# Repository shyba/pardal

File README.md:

# Pardal PCB

Command-line PCB place & route tool with a Python API and a Mojo backend route path.

## What this project covers

- Python-native board construction and routing workflows
- CLI flows for `build`, `place`, `route`, `drc`, and `repl`
- FreeRouting interop (`freeroute`)
- Mojo backend routing (`backend-route`) using KiCad 9 in Docker for extract/apply

## Requirements

- Python 3.10+
- Docker (required for `backend-route` and `freeroute`)
- KiCad on host is optional for backend-route/freeroute (Docker supplies KiCad 9 there)
- System `pcbnew` is required for `pardal-finalize`

## KiCad compatibility

- Full supported path: KiCad 9 (native or Docker-based tooling)
- Current default backend route path uses Docker image `kicad/kicad:9.0.6-full`
- Older host KiCad versions may still work for limited flows, but are not the full baseline

## Install

```bash
python3 -m venv venv
./venv/bin/pip install -U pip
./venv/bin/pip install -e .
```

Optional global shortcut:

```bash
pip install -e .
pardal --help
```

## CLI quickstart

```bash
# Show commands
./venv/bin/python -m pardal.cli --help

# Build from netlist (+ optional route)
pardal build project.net -p placement.txt -o board.kicad_pcb
pardal build project.net -p placement.txt -o board.kicad_pcb --route

# Route an existing PCB
pardal route board.kicad_pcb -o board_routed.kicad_pcb

# Run DRC
pardal drc board_routed.kicad_pcb --format text

# REPL
pardal repl
```

## Route DSL workflow

The route DSL commands stage artifacts only. They are not release-ready, JLC-ready, or orderable claims.

```bash
# Seed the checked-in example directory
pardal route-dsl example init --example-dir examples/routing_dsl

# Assemble the example artifacts and print the manifest path
pardal route-dsl example run --example-dir examples/routing_dsl

# Pure artifact stages
pardal route-dsl board-ir examples/routing_dsl/board_source.json -o examples/routing_dsl/board.ir.json
pardal route-dsl plan examples/routing_dsl/routes.pdl.yaml examples/routing_dsl/board.ir.json examples/routing_dsl/backend_manifest.json --route-plan-output examples/routing_dsl/route-plan.ir.json --artifact-output examples/routing_dsl/capability-report.json
pardal route-dsl candidates examples/routing_dsl/board.ir.json examples/routing_dsl/route-plan.ir.json examples/routing_dsl/backend_manifest.json -o examples/routing_dsl/route-candidates.json --routes examples/routing_dsl/routes.json

# Apply-to-copy: validate first, then copy input board bytes to the output board path and still write an apply report
pardal route-dsl apply examples/routing_dsl/board.ir.json examples/routing_dsl/route-plan.ir.json examples/routing_dsl/route-candidates.json -o examples/routing_dsl/apply-report.json --selected-candidate-id cand_rg_fpc_escape_a_0001 --input-board input.kicad_pcb --output-board output.kicad_pcb

# fpga-large staged finish-readiness lane
pardal route-dsl fpga-large prepare --work-dir /tmp/pardal-fpga-large
pardal route-dsl fpga-large resume --work-dir /tmp/pardal-fpga-large
pardal route-dsl fpga-large report --work-dir /tmp/pardal-fpga-large
```

## Mojo backend route quickstart

Routes an existing `.kicad_pcb` by extracting with KiCad 9 in Docker, routing on host backend, then applying back with KiCad 9 in Docker.

```bash
pardal backend-route input.kicad_pcb \
  -o output.kicad_pcb \
  --docker-image kicad/kicad:9.0.6-full \
  --cfg tests/fixtures/parity_fixtures/mojo_cfgs/strict_spacing.json \
  --extract-timeout-s 120 \
  --route-timeout-s 120 \
  --apply-timeout-s 120
```

Useful debug artifacts:

- `--problem-json /path/problem.json`
- `--routes-json /path/routes.json`

Deprecated alias:

- `pardal rust-route` (same behavior as `backend-route`, kept for compatibility)

## Python API quickstart

```python
from pathlib import Path
from pardal.board_builder import fpga_board
from pardal.routing_strategies import route_board
from pardal.kicad_writer import KicadWriter

board = (fpga_board(layers=4, width=40, height=40)
    .component("U1", "TQFP-32", (20, 20), value="FPGA")
    .component("C1", "0603", (12, 20), value="100nF")
    .net("VCC", "Power", [("U1", "8"), ("C1", "1")])
    .net("GND", "Power", [("U1", "16"), ("C1", "2")])
    .build())

result = route_board(board, "fpga")
print(f"Routed {result.nets_routed}/{result.nets_total} nets")

KicadWriter().write(board, Path("board.kicad_pcb"))
```

## Atopile handoff (minimal)

```bash
# Use the placed board produced by ato build
pardal route build/builds/default/default/default.kicad_pcb -o board_routed.kicad_pcb

# Optional: backend route instead of Python router
pardal backend-route build/builds/default/default/default.kicad_pcb -o board_routed.kicad_pcb

# Finalization uses system Python + pcbnew
/usr/bin/python3 -m pardal.finalize board_routed.kicad_pcb board_final.kicad_pcb
```

## Finalization

`pardal-finalize` (or `python -m pardal.finalize`) is the production-oriented step that replaces simplified footprints and rebuilds zones using system `pcbnew`.

## Testing

Fast checks:

```bash
./venv/bin/python -m pytest -q tests/test_cli.py tests/test_repl.py tests/test_api_io.py tests/test_route_command.py
./venv/bin/python -m pytest -q tests/integration/test_routing_scenarios.py tests/integration/test_variable_widths.py
```

## Troubleshooting

- `Error: docker permission denied`: ensure your user can access Docker daemon.
- `backend-route timed out`: increase `--extract-timeout-s`, `--route-timeout-s`, and `--apply-timeout-s`.
- Missing backend binary/config behavior: run without `--cfg` first, then add config incrementally.

## License

GNU Affero General Public License v3.0 (AGPL-3.0). See `LICENSE`.

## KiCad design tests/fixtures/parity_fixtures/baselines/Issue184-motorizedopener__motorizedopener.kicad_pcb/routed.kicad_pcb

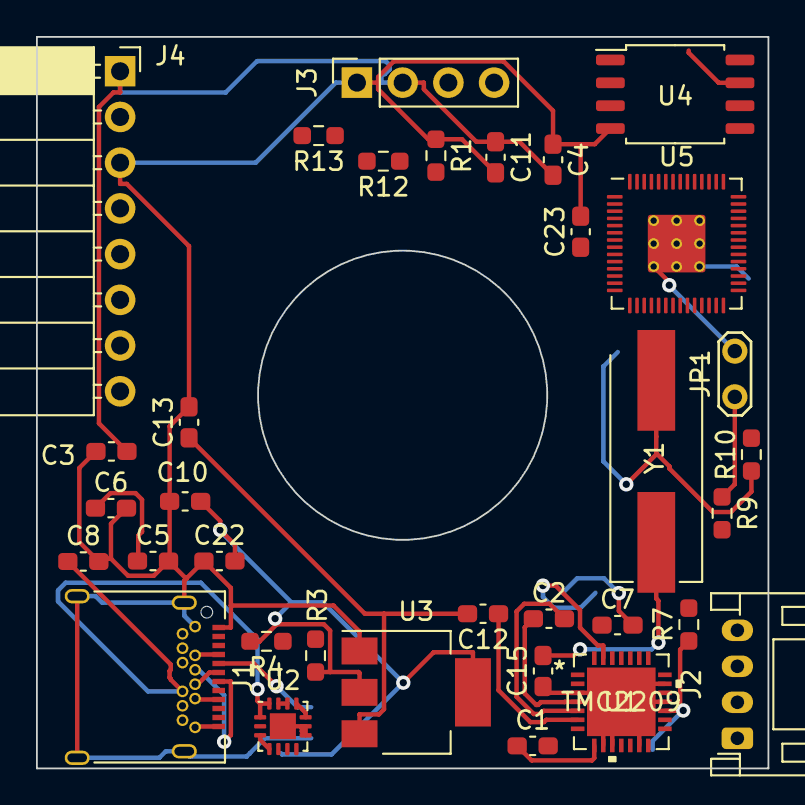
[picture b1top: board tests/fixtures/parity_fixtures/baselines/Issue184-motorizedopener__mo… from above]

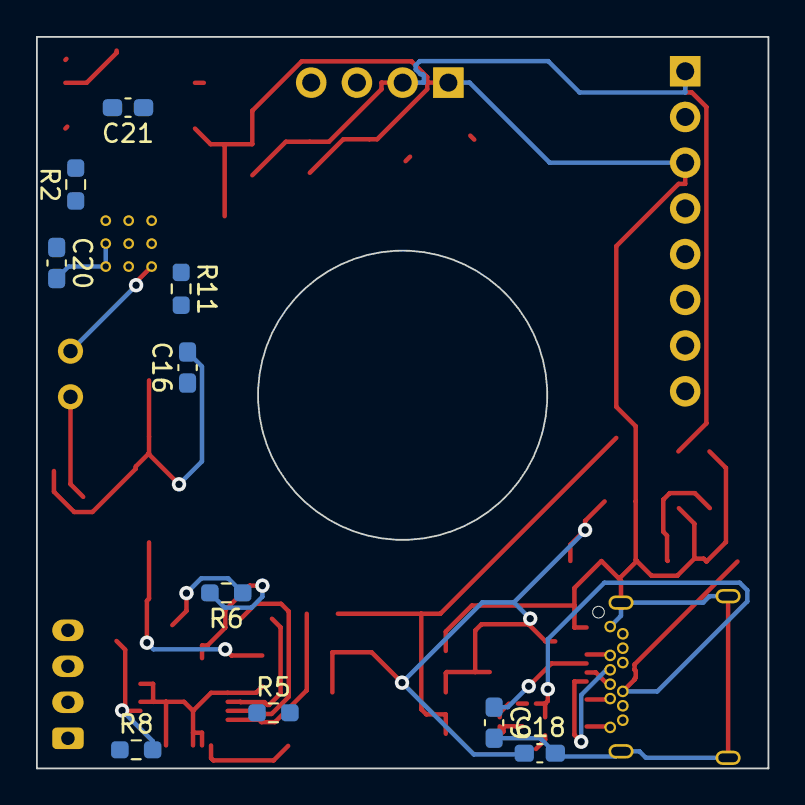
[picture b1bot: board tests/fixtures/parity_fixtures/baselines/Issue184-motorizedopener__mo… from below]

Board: 2 copper layers, 40.6 x 40.6 mm, 44 parts (10 on the bottom side), 49 nets.

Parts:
C1: 2.2uF; C_0603_1608Metric_Pad1.08x0.95mm_HandSolder
C2, C12: 22nF; C_0603_1608Metric_Pad1.08x0.95mm_HandSolder
C3, C21, C22: 1uF; C_0603_1608Metric_Pad1.08x0.95mm_HandSolder
C4, C6: 0.1uF; C_0603_1608Metric_Pad1.08x0.95mm_HandSolder
C5, C7, C11: 10uF; C_0603_1608Metric_Pad1.08x0.95mm_HandSolder
C8, C9: 470pF; C_0603_1608Metric_Pad1.08x0.95mm_HandSolder
C10, C18: 100nF; C_0603_1608Metric_Pad1.08x0.95mm_HandSolder
C13: 300nF; C_0603_1608Metric_Pad1.08x0.95mm_HandSolder
C15, C16: 27pF; C_0603_1608Metric_Pad1.08x0.95mm_HandSolder
C20: 200nF; C_0603_1608Metric_Pad1.08x0.95mm_HandSolder
C23: 700nF; C_0603_1608Metric_Pad1.08x0.95mm_HandSolder
J1: USB_C_Receptacle; USB_C_Receptacle_Amphenol_12401548E4-2A
J2: Stepper OUT; JST_PH_S4B-PH-K_1x04_P2.00mm_Horizontal
J3: I2C OLED; PinSocket_1x04_P2.54mm_Vertical
J4: SPI RFID; PinSocket_1x08_P2.54mm_Horizontal
JP1: Jumper_2_Open; TestPoint_2Pads_Pitch2.54mm_Drill0.8mm
R1, R7: 10k; R_0603_1608Metric_Pad0.98x0.95mm_HandSolder
R2, R3, R4: 4.7k; R_0603_1608Metric_Pad0.98x0.95mm_HandSolder
R5, R6: 220m; R_0603_1608Metric_Pad0.98x0.95mm_HandSolder
R8: 4.4k; R_0603_1608Metric_Pad0.98x0.95mm_HandSolder
R9, R10, R11: 1k; R_0603_1608Metric_Pad0.98x0.95mm_HandSolder
R12, R13: 27.4; R_0603_1608Metric_Pad0.98x0.95mm_HandSolder
U1: TMC2209
U2: FUSB302B01MPX; WQFN-14-1EP_2.5x2.5mm_P0.5mm_EP1.45x1.45mm
U3: NCP1117-3.3_SOT223; SOT-223-3_TabPin2
U4: W25Q128JVS; SOIC-8_5.23x5.23mm_P1.27mm
U5: RP2040; RP2040-QFN-56
Y1: 12.000MHZ; Crystal_SMD_HC49-US

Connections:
+1V1: C20.1, C21.2, U5.23 (DVDD), U5.45 (VREG_VOUT), U5.50 (DVDD)
+3V3: C3.2, C4.2, C10.1, C11.1, C18.1, C22.2, C23.1, J3.2, J4.1, R2.2, R3.2, R4.2, R7.2, U1.15 (VCC_IO), U2.3 (VDD), U2.4 (VDD), U3.2 (VO), U4.8 (VCC), U5.1 (IOVDD), U5.10 (IOVDD), U5.22 (IOVDD), U5.33 (IOVDD), U5.42 (IOVDD), U5.43 (ADC_AVDD), U5.44 (VREG_IN), U5.48 (USB_VDD), U5.49 (IOVDD)
GND: C1.2, C3.1, C4.1, C5.2, C6.2, C7.2, C8.2, C9.2, C10.2, C11.2, C13.2, C15.1, C16.1, C18.2, C20.2, C21.1, C22.1, C23.2, J1.A1 (GND), J1.A12 (GND), J1.B1 (GND), J1.B12 (GND), J1.S1 (SHIELD), J3.1, J4.3, JP1.1 (A), R1.1, R5.1, R6.1, R8.1, U1.3 (GND), U1.9 (MS1_AD0), U1.10 (MS2_AD1), U1.13 (CLK), U1.18 (GND), U1.20 (STDBY), U1.29 (GND), U2.8 (GND), U2.9 (GND), U2.15 (GND), U3.1 (GND), U4.4 (GND), U5.19 (TESTEN), U5.57 (GND)
unnamed: C1.1, U1.8 (5VOUT)
unnamed: C2.1, U1.4 (CPO)
unnamed: C2.2, U1.5 (CPI)
unnamed: C5.1, C6.1, U2.12 (VCONN), U2.13 (VCONN)
unnamed: C12.1, U1.6 (VCP)
unnamed: C15.2, U5.20 (XIN), Y1.1
unnamed: C16.2, R10.1, Y1.2
unnamed: J2.1, U1.26 (OB1)
unnamed: J2.2, U1.24 (OA1)
unnamed: J2.3, U1.21 (OA2)
unnamed: J2.4, U1.1 (OB2)
unnamed: J3.3, U5.30 (GPIO19)
unnamed: J3.4, U5.29 (GPIO18)
unnamed: J4.2, U5.9 (GPIO7)
unnamed: J4.4, U5.14 (GPIO11)
unnamed: J4.5, U5.15 (GPIO12)
unnamed: J4.6, U5.13 (GPIO10)
unnamed: J4.7, U5.16 (GPIO13)
unnamed: JP1.2 (B), R9.1
unnamed: R5.2, U1.23 (BRA)
unnamed: R6.2, U1.27 (BRB)
unnamed: R7.1, R8.2, U1.17 (VREF)
unnamed: R9.2, U4.1 (~CS), U5.56 (QSPI_SS)
unnamed: R10.2, U5.21 (XOUT)
unnamed: R11.1, U5.11 (GPIO8)
unnamed: R12.1, U5.47 (USB_DP)
unnamed: R13.1, U5.46 (USB_DM)
unnamed: U4.2 (DO(IO1)), U5.55 (QSPI_SD1)
unnamed: U4.3 (IO2), U5.54 (QSPI_SD2)
unnamed: U4.5 (DI(IO0)), U5.53 (QSPI_SD0)
unnamed: U4.6 (CLK), U5.52 (QSPI_SCLK)
unnamed: U4.7 (IO3), U5.51 (QSPI_SD3)
PWR-INT_N: R4.1, U2.5 (INT_N), U5.31 (GPIO20)
PWR-SCL: R3.1, U2.6 (SCL), U5.28 (GPIO17)
PWR-SDA: R2.1, U2.7 (SDA), U5.27 (GPIO16)
USB-D+: J1.A6 (D+), J1.B6 (D+), R12.2
USB-D-: J1.A7 (D-), J1.B7 (D-), R13.2
VBUS: C7.1, C12.2, C13.1, J1.A4 (VBUS), J1.A9 (VBUS), J1.B4 (VBUS), J1.B9 (VBUS), U1.22 (VS), U1.28 (VS), U2.2 (VBUS), U3.3 (VI)
cc1: C9.1, J1.A5 (CC1), U2.10 (CC1), U2.11 (CC1)
cc2: C8.1, J1.B5 (CC2), U2.1 (CC2), U2.14 (CC2)
tmc_DIAG: U1.11 (DIAG), U5.39 (GPIO27_ADC1)
tmc_DIR: U1.19 (DIR), U5.17 (GPIO14)
tmc_ENN: R1.2, U1.2 (ENN), U5.8 (GPIO6)
tmc_INDEX: U1.12 (INDEX), U5.38 (GPIO26_ADC0)
tmc_STEP: U1.16 (STEP), U5.18 (GPIO15)
tmc_UART: R11.2, U1.14 (PDN_UART), U5.12 (GPIO9)

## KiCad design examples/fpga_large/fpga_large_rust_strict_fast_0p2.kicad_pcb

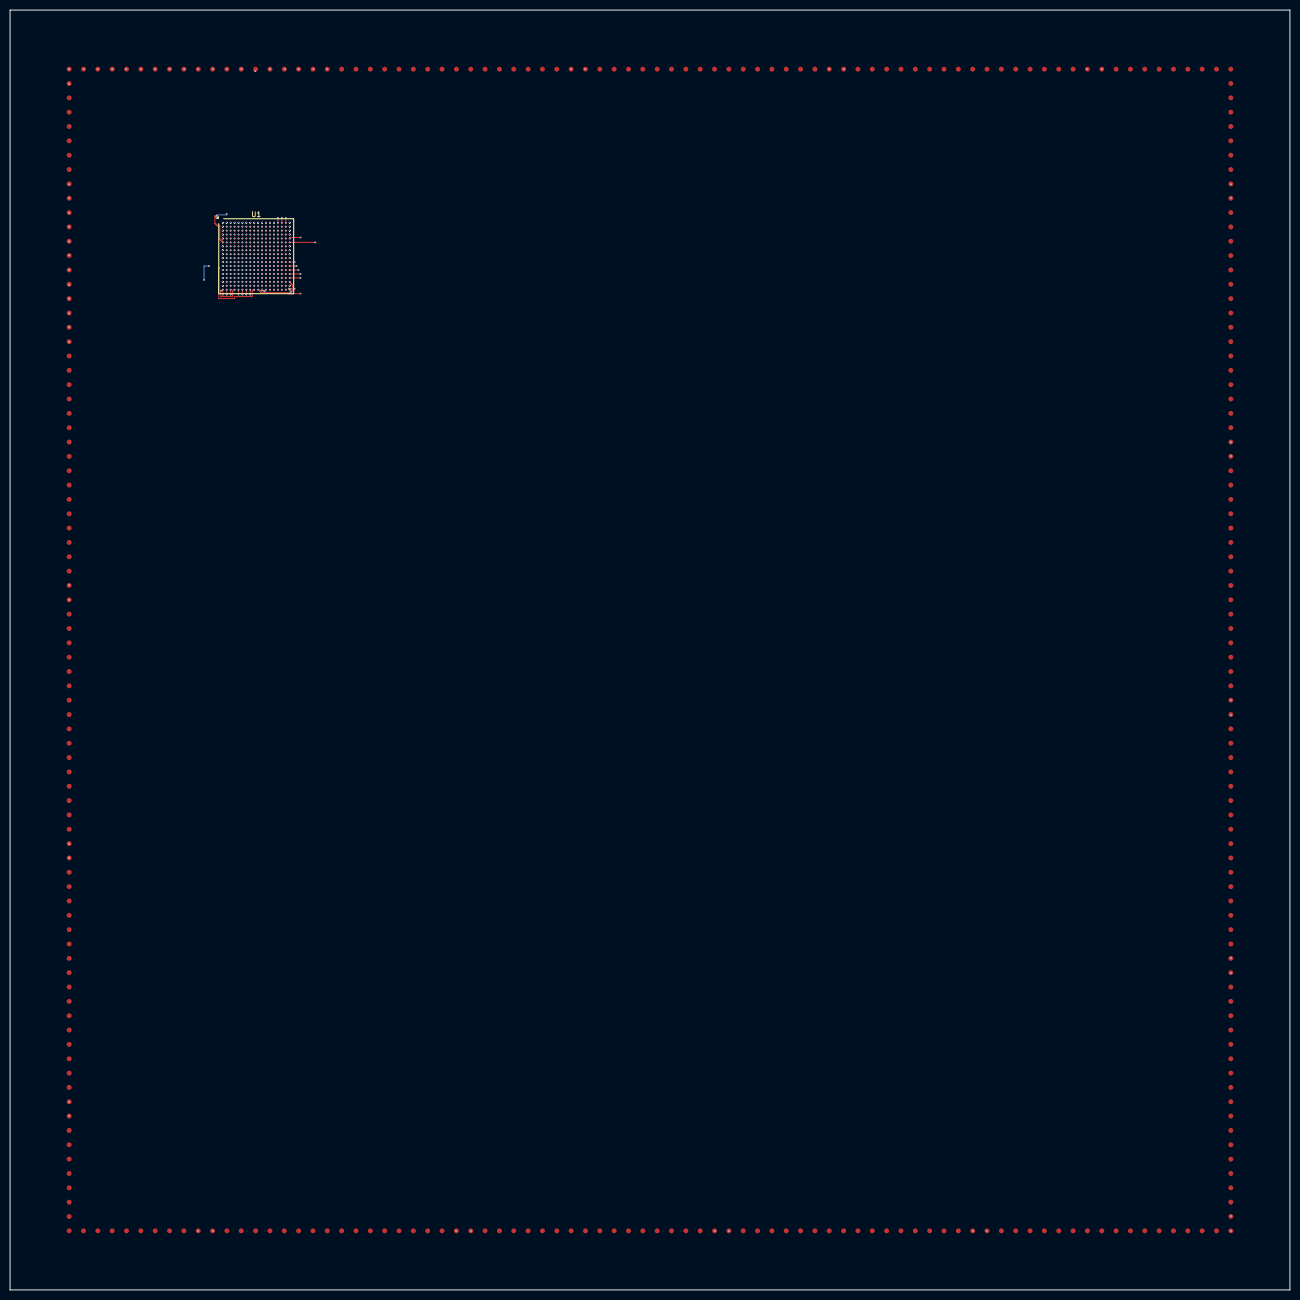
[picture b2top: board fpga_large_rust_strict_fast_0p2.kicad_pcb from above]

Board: 4 copper layers, 260.0 x 260.0 mm, 325 parts (0 on the bottom side), 324 nets.

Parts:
TP1: A1; TestPoint_Pad_D1.0mm
TP2: A2; TestPoint_Pad_D1.0mm
TP3: A3; TestPoint_Pad_D1.0mm
TP4: A4; TestPoint_Pad_D1.0mm
TP5: A5; TestPoint_Pad_D1.0mm
TP6: A6; TestPoint_Pad_D1.0mm
TP7: A7; TestPoint_Pad_D1.0mm
TP8: A8; TestPoint_Pad_D1.0mm
TP9: A9; TestPoint_Pad_D1.0mm
TP10: A10; TestPoint_Pad_D1.0mm
TP11: A11; TestPoint_Pad_D1.0mm
TP12: A12; TestPoint_Pad_D1.0mm
TP13: A13; TestPoint_Pad_D1.0mm
TP14: A14; TestPoint_Pad_D1.0mm
TP15: A15; TestPoint_Pad_D1.0mm
TP16: A16; TestPoint_Pad_D1.0mm
TP17: A17; TestPoint_Pad_D1.0mm
TP18: A18; TestPoint_Pad_D1.0mm
TP19: B1; TestPoint_Pad_D1.0mm
TP20: B2; TestPoint_Pad_D1.0mm
TP21: B3; TestPoint_Pad_D1.0mm
TP22: B4; TestPoint_Pad_D1.0mm
TP23: B5; TestPoint_Pad_D1.0mm
TP24: B6; TestPoint_Pad_D1.0mm
TP25: B7; TestPoint_Pad_D1.0mm
TP26: B8; TestPoint_Pad_D1.0mm
TP27: B9; TestPoint_Pad_D1.0mm
TP28: B10; TestPoint_Pad_D1.0mm
TP29: B11; TestPoint_Pad_D1.0mm
TP30: B12; TestPoint_Pad_D1.0mm
TP31: B13; TestPoint_Pad_D1.0mm
TP32: B14; TestPoint_Pad_D1.0mm
TP33: B15; TestPoint_Pad_D1.0mm
TP34: B16; TestPoint_Pad_D1.0mm
TP35: B17; TestPoint_Pad_D1.0mm
TP36: B18; TestPoint_Pad_D1.0mm
TP37: C1; TestPoint_Pad_D1.0mm
TP38: C2; TestPoint_Pad_D1.0mm
TP39: C3; TestPoint_Pad_D1.0mm
TP40: C4; TestPoint_Pad_D1.0mm
TP41: C5; TestPoint_Pad_D1.0mm
TP42: C6; TestPoint_Pad_D1.0mm
TP43: C7; TestPoint_Pad_D1.0mm
TP44: C8; TestPoint_Pad_D1.0mm
TP45: C9; TestPoint_Pad_D1.0mm
TP46: C10; TestPoint_Pad_D1.0mm
TP47: C11; TestPoint_Pad_D1.0mm
TP48: C12; TestPoint_Pad_D1.0mm
TP49: C13; TestPoint_Pad_D1.0mm
TP50: C14; TestPoint_Pad_D1.0mm
TP51: C15; TestPoint_Pad_D1.0mm
TP52: C16; TestPoint_Pad_D1.0mm
TP53: C17; TestPoint_Pad_D1.0mm
TP54: C18; TestPoint_Pad_D1.0mm
TP55: D1; TestPoint_Pad_D1.0mm
TP56: D2; TestPoint_Pad_D1.0mm
TP57: D3; TestPoint_Pad_D1.0mm
TP58: D4; TestPoint_Pad_D1.0mm
TP59: D5; TestPoint_Pad_D1.0mm
TP60: D6; TestPoint_Pad_D1.0mm
TP61: D7; TestPoint_Pad_D1.0mm
TP62: D8; TestPoint_Pad_D1.0mm
TP63: D9; TestPoint_Pad_D1.0mm
TP64: D10; TestPoint_Pad_D1.0mm
TP65: D11; TestPoint_Pad_D1.0mm
TP66: D12; TestPoint_Pad_D1.0mm
TP67: D13; TestPoint_Pad_D1.0mm
TP68: D14; TestPoint_Pad_D1.0mm
TP69: D15; TestPoint_Pad_D1.0mm
TP70: D16; TestPoint_Pad_D1.0mm
TP71: D17; TestPoint_Pad_D1.0mm
TP72: D18; TestPoint_Pad_D1.0mm
TP73: E1; TestPoint_Pad_D1.0mm
TP74: E2; TestPoint_Pad_D1.0mm
TP75: E3; TestPoint_Pad_D1.0mm
TP76: E4; TestPoint_Pad_D1.0mm
TP77: E5; TestPoint_Pad_D1.0mm
TP78: E6; TestPoint_Pad_D1.0mm
TP79: E7; TestPoint_Pad_D1.0mm
TP80: E8; TestPoint_Pad_D1.0mm
TP81: E9; TestPoint_Pad_D1.0mm
TP82: E10; TestPoint_Pad_D1.0mm
TP83: E11; TestPoint_Pad_D1.0mm
TP84: E12; TestPoint_Pad_D1.0mm
TP85: E13; TestPoint_Pad_D1.0mm
TP86: E14; TestPoint_Pad_D1.0mm
TP87: E15; TestPoint_Pad_D1.0mm
TP88: E16; TestPoint_Pad_D1.0mm
TP89: E17; TestPoint_Pad_D1.0mm
TP90: E18; TestPoint_Pad_D1.0mm
TP91: F1; TestPoint_Pad_D1.0mm
TP92: F2; TestPoint_Pad_D1.0mm
TP93: F3; TestPoint_Pad_D1.0mm
TP94: F4; TestPoint_Pad_D1.0mm
TP95: F5; TestPoint_Pad_D1.0mm
TP96: F6; TestPoint_Pad_D1.0mm
TP97: F7; TestPoint_Pad_D1.0mm
TP98: F8; TestPoint_Pad_D1.0mm
TP99: F9; TestPoint_Pad_D1.0mm
TP100: F10; TestPoint_Pad_D1.0mm
TP101: F11; TestPoint_Pad_D1.0mm
TP102: F12; TestPoint_Pad_D1.0mm
TP103: F13; TestPoint_Pad_D1.0mm
TP104: F14; TestPoint_Pad_D1.0mm
TP105: F15; TestPoint_Pad_D1.0mm
TP106: F16; TestPoint_Pad_D1.0mm
TP107: F17; TestPoint_Pad_D1.0mm
TP108: F18; TestPoint_Pad_D1.0mm
TP109: G1; TestPoint_Pad_D1.0mm
TP110: G2; TestPoint_Pad_D1.0mm
TP111: G3; TestPoint_Pad_D1.0mm
TP112: G4; TestPoint_Pad_D1.0mm
TP113: G5; TestPoint_Pad_D1.0mm
TP114: G6; TestPoint_Pad_D1.0mm
TP115: G7; TestPoint_Pad_D1.0mm
TP116: G8; TestPoint_Pad_D1.0mm
TP117: G9; TestPoint_Pad_D1.0mm
TP118: G10; TestPoint_Pad_D1.0mm
TP119: G11; TestPoint_Pad_D1.0mm
TP120: G12; TestPoint_Pad_D1.0mm
TP121: G13; TestPoint_Pad_D1.0mm
TP122: G14; TestPoint_Pad_D1.0mm
TP123: G15; TestPoint_Pad_D1.0mm
TP124: G16; TestPoint_Pad_D1.0mm
TP125: G17; TestPoint_Pad_D1.0mm
TP126: G18; TestPoint_Pad_D1.0mm
TP127: H1; TestPoint_Pad_D1.0mm
TP128: H2; TestPoint_Pad_D1.0mm
TP129: H3; TestPoint_Pad_D1.0mm
TP130: H4; TestPoint_Pad_D1.0mm
TP131: H5; TestPoint_Pad_D1.0mm
TP132: H6; TestPoint_Pad_D1.0mm
TP133: H7; TestPoint_Pad_D1.0mm
TP134: H8; TestPoint_Pad_D1.0mm
TP135: H9; TestPoint_Pad_D1.0mm
TP136: H10; TestPoint_Pad_D1.0mm
TP137: H11; TestPoint_Pad_D1.0mm
TP138: H12; TestPoint_Pad_D1.0mm
TP139: H13; TestPoint_Pad_D1.0mm
TP140: H14; TestPoint_Pad_D1.0mm
TP141: H15; TestPoint_Pad_D1.0mm
TP142: H16; TestPoint_Pad_D1.0mm
TP143: H17; TestPoint_Pad_D1.0mm
TP144: H18; TestPoint_Pad_D1.0mm
TP145: J1; TestPoint_Pad_D1.0mm
TP146: J2; TestPoint_Pad_D1.0mm
TP147: J3; TestPoint_Pad_D1.0mm
TP148: J4; TestPoint_Pad_D1.0mm
TP149: J5; TestPoint_Pad_D1.0mm
TP150: J6; TestPoint_Pad_D1.0mm
TP151: J7; TestPoint_Pad_D1.0mm
TP152: J8; TestPoint_Pad_D1.0mm
TP153: J9; TestPoint_Pad_D1.0mm
TP154: J10; TestPoint_Pad_D1.0mm
TP155: J11; TestPoint_Pad_D1.0mm
TP156: J12; TestPoint_Pad_D1.0mm
TP157: J13; TestPoint_Pad_D1.0mm
TP158: J14; TestPoint_Pad_D1.0mm
TP159: J15; TestPoint_Pad_D1.0mm
TP160: J16; TestPoint_Pad_D1.0mm
TP161: J17; TestPoint_Pad_D1.0mm
TP162: J18; TestPoint_Pad_D1.0mm
TP163: K1; TestPoint_Pad_D1.0mm
TP164: K2; TestPoint_Pad_D1.0mm
TP165: K3; TestPoint_Pad_D1.0mm
TP166: K4; TestPoint_Pad_D1.0mm
TP167: K5; TestPoint_Pad_D1.0mm
TP168: K6; TestPoint_Pad_D1.0mm
TP169: K7; TestPoint_Pad_D1.0mm
TP170: K8; TestPoint_Pad_D1.0mm
TP171: K9; TestPoint_Pad_D1.0mm
TP172: K10; TestPoint_Pad_D1.0mm
TP173: K11; TestPoint_Pad_D1.0mm
TP174: K12; TestPoint_Pad_D1.0mm
TP175: K13; TestPoint_Pad_D1.0mm
TP176: K14; TestPoint_Pad_D1.0mm
TP177: K15; TestPoint_Pad_D1.0mm
TP178: K16; TestPoint_Pad_D1.0mm
TP179: K17; TestPoint_Pad_D1.0mm
TP180: K18; TestPoint_Pad_D1.0mm
TP181: L1; TestPoint_Pad_D1.0mm
TP182: L2; TestPoint_Pad_D1.0mm
TP183: L3; TestPoint_Pad_D1.0mm
TP184: L4; TestPoint_Pad_D1.0mm
TP185: L5; TestPoint_Pad_D1.0mm
TP186: L6; TestPoint_Pad_D1.0mm
TP187: L7; TestPoint_Pad_D1.0mm
TP188: L8; TestPoint_Pad_D1.0mm
TP189: L9; TestPoint_Pad_D1.0mm
TP190: L10; TestPoint_Pad_D1.0mm
TP191: L11; TestPoint_Pad_D1.0mm
TP192: L12; TestPoint_Pad_D1.0mm
TP193: L13; TestPoint_Pad_D1.0mm
TP194: L14; TestPoint_Pad_D1.0mm
TP195: L15; TestPoint_Pad_D1.0mm
TP196: L16; TestPoint_Pad_D1.0mm
TP197: L17; TestPoint_Pad_D1.0mm
TP198: L18; TestPoint_Pad_D1.0mm
TP199: M1; TestPoint_Pad_D1.0mm
TP200: M2; TestPoint_Pad_D1.0mm
TP201: M3; TestPoint_Pad_D1.0mm
TP202: M4; TestPoint_Pad_D1.0mm
TP203: M5; TestPoint_Pad_D1.0mm
TP204: M6; TestPoint_Pad_D1.0mm
TP205: M7; TestPoint_Pad_D1.0mm
TP206: M8; TestPoint_Pad_D1.0mm
TP207: M9; TestPoint_Pad_D1.0mm
TP208: M10; TestPoint_Pad_D1.0mm
TP209: M11; TestPoint_Pad_D1.0mm
TP210: M12; TestPoint_Pad_D1.0mm
TP211: M13; TestPoint_Pad_D1.0mm
TP212: M14; TestPoint_Pad_D1.0mm
TP213: M15; TestPoint_Pad_D1.0mm
TP214: M16; TestPoint_Pad_D1.0mm
TP215: M17; TestPoint_Pad_D1.0mm
TP216: M18; TestPoint_Pad_D1.0mm
TP217: N1; TestPoint_Pad_D1.0mm
TP218: N2; TestPoint_Pad_D1.0mm
TP219: N3; TestPoint_Pad_D1.0mm
TP220: N4; TestPoint_Pad_D1.0mm
TP221: N5; TestPoint_Pad_D1.0mm
TP222: N6; TestPoint_Pad_D1.0mm
TP223: N7; TestPoint_Pad_D1.0mm
TP224: N8; TestPoint_Pad_D1.0mm
TP225: N9; TestPoint_Pad_D1.0mm
TP226: N10; TestPoint_Pad_D1.0mm
TP227: N11; TestPoint_Pad_D1.0mm
TP228: N12; TestPoint_Pad_D1.0mm
TP229: N13; TestPoint_Pad_D1.0mm
TP230: N14; TestPoint_Pad_D1.0mm
TP231: N15; TestPoint_Pad_D1.0mm
TP232: N16; TestPoint_Pad_D1.0mm
TP233: N17; TestPoint_Pad_D1.0mm
TP234: N18; TestPoint_Pad_D1.0mm
TP235: P1; TestPoint_Pad_D1.0mm
TP236: P2; TestPoint_Pad_D1.0mm
TP237: P3; TestPoint_Pad_D1.0mm
TP238: P4; TestPoint_Pad_D1.0mm
TP239: P5; TestPoint_Pad_D1.0mm
TP240: P6; TestPoint_Pad_D1.0mm
TP241: P7; TestPoint_Pad_D1.0mm
TP242: P8; TestPoint_Pad_D1.0mm
TP243: P9; TestPoint_Pad_D1.0mm
TP244: P10; TestPoint_Pad_D1.0mm
TP245: P11; TestPoint_Pad_D1.0mm
TP246: P12; TestPoint_Pad_D1.0mm
TP247: P13; TestPoint_Pad_D1.0mm
TP248: P14; TestPoint_Pad_D1.0mm
TP249: P15; TestPoint_Pad_D1.0mm
TP250: P16; TestPoint_Pad_D1.0mm
TP251: P17; TestPoint_Pad_D1.0mm
TP252: P18; TestPoint_Pad_D1.0mm
TP253: R1; TestPoint_Pad_D1.0mm
TP254: R2; TestPoint_Pad_D1.0mm
TP255: R3; TestPoint_Pad_D1.0mm
TP256: R4; TestPoint_Pad_D1.0mm
TP257: R5; TestPoint_Pad_D1.0mm
TP258: R6; TestPoint_Pad_D1.0mm
TP259: R7; TestPoint_Pad_D1.0mm
TP260: R8; TestPoint_Pad_D1.0mm
TP261: R9; TestPoint_Pad_D1.0mm
TP262: R10; TestPoint_Pad_D1.0mm
TP263: R11; TestPoint_Pad_D1.0mm
TP264: R12; TestPoint_Pad_D1.0mm
TP265: R13; TestPoint_Pad_D1.0mm
TP266: R14; TestPoint_Pad_D1.0mm
TP267: R15; TestPoint_Pad_D1.0mm
TP268: R16; TestPoint_Pad_D1.0mm
TP269: R17; TestPoint_Pad_D1.0mm
TP270: R18; TestPoint_Pad_D1.0mm
TP271: T1; TestPoint_Pad_D1.0mm
TP272: T2; TestPoint_Pad_D1.0mm
TP273: T3; TestPoint_Pad_D1.0mm
TP274: T4; TestPoint_Pad_D1.0mm
TP275: T5; TestPoint_Pad_D1.0mm
TP276: T6; TestPoint_Pad_D1.0mm
TP277: T7; TestPoint_Pad_D1.0mm
TP278: T8; TestPoint_Pad_D1.0mm
TP279: T9; TestPoint_Pad_D1.0mm
TP280: T10; TestPoint_Pad_D1.0mm
TP281: T11; TestPoint_Pad_D1.0mm
TP282: T12; TestPoint_Pad_D1.0mm
TP283: T13; TestPoint_Pad_D1.0mm
TP284: T14; TestPoint_Pad_D1.0mm
TP285: T15; TestPoint_Pad_D1.0mm
TP286: T16; TestPoint_Pad_D1.0mm
TP287: T17; TestPoint_Pad_D1.0mm
TP288: T18; TestPoint_Pad_D1.0mm
TP289: U1; TestPoint_Pad_D1.0mm
TP290: U2; TestPoint_Pad_D1.0mm
TP291: U3; TestPoint_Pad_D1.0mm
TP292: U4; TestPoint_Pad_D1.0mm
TP293: U5; TestPoint_Pad_D1.0mm
TP294: U6; TestPoint_Pad_D1.0mm
TP295: U7; TestPoint_Pad_D1.0mm
TP296: U8; TestPoint_Pad_D1.0mm
TP297: U9; TestPoint_Pad_D1.0mm
TP298: U10; TestPoint_Pad_D1.0mm
TP299: U11; TestPoint_Pad_D1.0mm
TP300: U12; TestPoint_Pad_D1.0mm
TP301: U13; TestPoint_Pad_D1.0mm
TP302: U14; TestPoint_Pad_D1.0mm
TP303: U15; TestPoint_Pad_D1.0mm
TP304: U16; TestPoint_Pad_D1.0mm
TP305: U17; TestPoint_Pad_D1.0mm
TP306: U18; TestPoint_Pad_D1.0mm
TP307: V1; TestPoint_Pad_D1.0mm
TP308: V2; TestPoint_Pad_D1.0mm
TP309: V3; TestPoint_Pad_D1.0mm
TP310: V4; TestPoint_Pad_D1.0mm
TP311: V5; TestPoint_Pad_D1.0mm
TP312: V6; TestPoint_Pad_D1.0mm
TP313: V7; TestPoint_Pad_D1.0mm
TP314: V8; TestPoint_Pad_D1.0mm
TP315: V9; TestPoint_Pad_D1.0mm
TP316: V10; TestPoint_Pad_D1.0mm
TP317: V11; TestPoint_Pad_D1.0mm
TP318: V12; TestPoint_Pad_D1.0mm
TP319: V13; TestPoint_Pad_D1.0mm
TP320: V14; TestPoint_Pad_D1.0mm
TP321: V15; TestPoint_Pad_D1.0mm
TP322: V16; TestPoint_Pad_D1.0mm
TP323: V17; TestPoint_Pad_D1.0mm
TP324: V18; TestPoint_Pad_D1.0mm
U1: XC6SLX25-CSG324; Xilinx_CSG324

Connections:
U1_A1: TP1.1, U1.A1
U1_A2: TP2.1, U1.A2
U1_A3: TP3.1, U1.A3
U1_A4: TP4.1, U1.A4
U1_A5: TP5.1, U1.A5
U1_A6: TP6.1, U1.A6
U1_A7: TP7.1, U1.A7
U1_A8: TP8.1, U1.A8
U1_A9: TP9.1, U1.A9
U1_A10: TP10.1, U1.A10
U1_A11: TP11.1, U1.A11
U1_A12: TP12.1, U1.A12
U1_A13: TP13.1, U1.A13
U1_A14: TP14.1, U1.A14
U1_A15: TP15.1, U1.A15
U1_A16: TP16.1, U1.A16
U1_A17: TP17.1, U1.A17
U1_A18: TP18.1, U1.A18
U1_B1: TP19.1, U1.B1
U1_B2: TP20.1, U1.B2
U1_B3: TP21.1, U1.B3
U1_B4: TP22.1, U1.B4
U1_B5: TP23.1, U1.B5
U1_B6: TP24.1, U1.B6
U1_B7: TP25.1, U1.B7
U1_B8: TP26.1, U1.B8
U1_B9: TP27.1, U1.B9
U1_B10: TP28.1, U1.B10
U1_B11: TP29.1, U1.B11
U1_B12: TP30.1, U1.B12
U1_B13: TP31.1, U1.B13
U1_B14: TP32.1, U1.B14
U1_B15: TP33.1, U1.B15
U1_B16: TP34.1, U1.B16
U1_B17: TP35.1, U1.B17
U1_B18: TP36.1, U1.B18
U1_C1: TP37.1, U1.C1
U1_C2: TP38.1, U1.C2
U1_C3: TP39.1, U1.C3
U1_C4: TP40.1, U1.C4
U1_C5: TP41.1, U1.C5
U1_C6: TP42.1, U1.C6
U1_C7: TP43.1, U1.C7
U1_C8: TP44.1, U1.C8
U1_C9: TP45.1, U1.C9
U1_C10: TP46.1, U1.C10
U1_C11: TP47.1, U1.C11
U1_C12: TP48.1, U1.C12
U1_C13: TP49.1, U1.C13
U1_C14: TP50.1, U1.C14
U1_C15: TP51.1, U1.C15
U1_C16: TP52.1, U1.C16
U1_C17: TP53.1, U1.C17
U1_C18: TP54.1, U1.C18
U1_D1: TP55.1, U1.D1
U1_D2: TP56.1, U1.D2
U1_D3: TP57.1, U1.D3
U1_D4: TP58.1, U1.D4
U1_D5: TP59.1, U1.D5
U1_D6: TP60.1, U1.D6
U1_D7: TP61.1, U1.D7
U1_D8: TP62.1, U1.D8
U1_D9: TP63.1, U1.D9
U1_D10: TP64.1, U1.D10
U1_D11: TP65.1, U1.D11
U1_D12: TP66.1, U1.D12
U1_D13: TP67.1, U1.D13
U1_D14: TP68.1, U1.D14
U1_D15: TP69.1, U1.D15
U1_D16: TP70.1, U1.D16
U1_D17: TP71.1, U1.D17
U1_D18: TP72.1, U1.D18
U1_E1: TP73.1, U1.E1
U1_E2: TP74.1, U1.E2
U1_E3: TP75.1, U1.E3
U1_E4: TP76.1, U1.E4
U1_E5: TP77.1, U1.E5
U1_E6: TP78.1, U1.E6
U1_E7: TP79.1, U1.E7
U1_E8: TP80.1, U1.E8
U1_E9: TP81.1, U1.E9
U1_E10: TP82.1, U1.E10
U1_E11: TP83.1, U1.E11
U1_E12: TP84.1, U1.E12
U1_E13: TP85.1, U1.E13
U1_E14: TP86.1, U1.E14
U1_E15: TP87.1, U1.E15
U1_E16: TP88.1, U1.E16
U1_E17: TP89.1, U1.E17
U1_E18: TP90.1, U1.E18
U1_F1: TP91.1, U1.F1
U1_F2: TP92.1, U1.F2
U1_F3: TP93.1, U1.F3
U1_F4: TP94.1, U1.F4
U1_F5: TP95.1, U1.F5
U1_F6: TP96.1, U1.F6
U1_F7: TP97.1, U1.F7
U1_F8: TP98.1, U1.F8
U1_F9: TP99.1, U1.F9
U1_F10: TP100.1, U1.F10
U1_F11: TP101.1, U1.F11
U1_F12: TP102.1, U1.F12
U1_F13: TP103.1, U1.F13
U1_F14: TP104.1, U1.F14
U1_F15: TP105.1, U1.F15
U1_F16: TP106.1, U1.F16
U1_F17: TP107.1, U1.F17
U1_F18: TP108.1, U1.F18
U1_G1: TP109.1, U1.G1
U1_G2: TP110.1, U1.G2
U1_G3: TP111.1, U1.G3
U1_G4: TP112.1, U1.G4
U1_G5: TP113.1, U1.G5
U1_G6: TP114.1, U1.G6
U1_G7: TP115.1, U1.G7
U1_G8: TP116.1, U1.G8
U1_G9: TP117.1, U1.G9
U1_G10: TP118.1, U1.G10
U1_G11: TP119.1, U1.G11
U1_G12: TP120.1, U1.G12
U1_G13: TP121.1, U1.G13
U1_G14: TP122.1, U1.G14
U1_G15: TP123.1, U1.G15
U1_G16: TP124.1, U1.G16
U1_G17: TP125.1, U1.G17
U1_G18: TP126.1, U1.G18
U1_H1: TP127.1, U1.H1
U1_H2: TP128.1, U1.H2
U1_H3: TP129.1, U1.H3
U1_H4: TP130.1, U1.H4
U1_H5: TP131.1, U1.H5
U1_H6: TP132.1, U1.H6
U1_H7: TP133.1, U1.H7
U1_H8: TP134.1, U1.H8
U1_H9: TP135.1, U1.H9
U1_H10: TP136.1, U1.H10
U1_H11: TP137.1, U1.H11
U1_H12: TP138.1, U1.H12
U1_H13: TP139.1, U1.H13
U1_H14: TP140.1, U1.H14
U1_H15: TP141.1, U1.H15
U1_H16: TP142.1, U1.H16
U1_H17: TP143.1, U1.H17
U1_H18: TP144.1, U1.H18
U1_J1: TP145.1, U1.J1
U1_J2: TP146.1, U1.J2
U1_J3: TP147.1, U1.J3
U1_J4: TP148.1, U1.J4
U1_J5: TP149.1, U1.J5
U1_J6: TP150.1, U1.J6
U1_J7: TP151.1, U1.J7
U1_J8: TP152.1, U1.J8
U1_J9: TP153.1, U1.J9
U1_J10: TP154.1, U1.J10
U1_J11: TP155.1, U1.J11
U1_J12: TP156.1, U1.J12
U1_J13: TP157.1, U1.J13
U1_J14: TP158.1, U1.J14
U1_J15: TP159.1, U1.J15
U1_J16: TP160.1, U1.J16
U1_J17: TP161.1, U1.J17
U1_J18: TP162.1, U1.J18
U1_K1: TP163.1, U1.K1
U1_K2: TP164.1, U1.K2
U1_K3: TP165.1, U1.K3
U1_K4: TP166.1, U1.K4
U1_K5: TP167.1, U1.K5
U1_K6: TP168.1, U1.K6
U1_K7: TP169.1, U1.K7
U1_K8: TP170.1, U1.K8
U1_K9: TP171.1, U1.K9
U1_K10: TP172.1, U1.K10
U1_K11: TP173.1, U1.K11
U1_K12: TP174.1, U1.K12
U1_K13: TP175.1, U1.K13
U1_K14: TP176.1, U1.K14
U1_K15: TP177.1, U1.K15
U1_K16: TP178.1, U1.K16
U1_K17: TP179.1, U1.K17
U1_K18: TP180.1, U1.K18
U1_L1: TP181.1, U1.L1
U1_L2: TP182.1, U1.L2
U1_L3: TP183.1, U1.L3
U1_L4: TP184.1, U1.L4
U1_L5: TP185.1, U1.L5
U1_L6: TP186.1, U1.L6
U1_L7: TP187.1, U1.L7
U1_L8: TP188.1, U1.L8
U1_L9: TP189.1, U1.L9
U1_L10: TP190.1, U1.L10
U1_L11: TP191.1, U1.L11
U1_L12: TP192.1, U1.L12
U1_L13: TP193.1, U1.L13
U1_L14: TP194.1, U1.L14
U1_L15: TP195.1, U1.L15
U1_L16: TP196.1, U1.L16
U1_L17: TP197.1, U1.L17
U1_L18: TP198.1, U1.L18
U1_M1: TP199.1, U1.M1
U1_M2: TP200.1, U1.M2
U1_M3: TP201.1, U1.M3
U1_M4: TP202.1, U1.M4
U1_M5: TP203.1, U1.M5
U1_M6: TP204.1, U1.M6
U1_M7: TP205.1, U1.M7
U1_M8: TP206.1, U1.M8
U1_M9: TP207.1, U1.M9
U1_M10: TP208.1, U1.M10
U1_M11: TP209.1, U1.M11
U1_M12: TP210.1, U1.M12
U1_M13: TP211.1, U1.M13
U1_M14: TP212.1, U1.M14
U1_M15: TP213.1, U1.M15
U1_M16: TP214.1, U1.M16
U1_M17: TP215.1, U1.M17
U1_M18: TP216.1, U1.M18
U1_N1: TP217.1, U1.N1
U1_N2: TP218.1, U1.N2
U1_N3: TP219.1, U1.N3
U1_N4: TP220.1, U1.N4
U1_N5: TP221.1, U1.N5
U1_N6: TP222.1, U1.N6
U1_N7: TP223.1, U1.N7
U1_N8: TP224.1, U1.N8
U1_N9: TP225.1, U1.N9
U1_N10: TP226.1, U1.N10
U1_N11: TP227.1, U1.N11
U1_N12: TP228.1, U1.N12
U1_N13: TP229.1, U1.N13
U1_N14: TP230.1, U1.N14
U1_N15: TP231.1, U1.N15
U1_N16: TP232.1, U1.N16
U1_N17: TP233.1, U1.N17
U1_N18: TP234.1, U1.N18
U1_P1: TP235.1, U1.P1
U1_P2: TP236.1, U1.P2
U1_P3: TP237.1, U1.P3
U1_P4: TP238.1, U1.P4
U1_P5: TP239.1, U1.P5
U1_P6: TP240.1, U1.P6
U1_P7: TP241.1, U1.P7
U1_P8: TP242.1, U1.P8
U1_P9: TP243.1, U1.P9
U1_P10: TP244.1, U1.P10
U1_P11: TP245.1, U1.P11
U1_P12: TP246.1, U1.P12
U1_P13: TP247.1, U1.P13
U1_P14: TP248.1, U1.P14
U1_P15: TP249.1, U1.P15
U1_P16: TP250.1, U1.P16
U1_P17: TP251.1, U1.P17
U1_P18: TP252.1, U1.P18
U1_R1: TP253.1, U1.R1
U1_R2: TP254.1, U1.R2
U1_R3: TP255.1, U1.R3
U1_R4: TP256.1, U1.R4
U1_R5: TP257.1, U1.R5
U1_R6: TP258.1, U1.R6
U1_R7: TP259.1, U1.R7
U1_R8: TP260.1, U1.R8
U1_R9: TP261.1, U1.R9
U1_R10: TP262.1, U1.R10
U1_R11: TP263.1, U1.R11
U1_R12: TP264.1, U1.R12
U1_R13: TP265.1, U1.R13
U1_R14: TP266.1, U1.R14
U1_R15: TP267.1, U1.R15
U1_R16: TP268.1, U1.R16
U1_R17: TP269.1, U1.R17
U1_R18: TP270.1, U1.R18
U1_T1: TP271.1, U1.T1
U1_T2: TP272.1, U1.T2
U1_T3: TP273.1, U1.T3
U1_T4: TP274.1, U1.T4
U1_T5: TP275.1, U1.T5
U1_T6: TP276.1, U1.T6
U1_T7: TP277.1, U1.T7
U1_T8: TP278.1, U1.T8
U1_T9: TP279.1, U1.T9
U1_T10: TP280.1, U1.T10
U1_T11: TP281.1, U1.T11
U1_T12: TP282.1, U1.T12
U1_T13: TP283.1, U1.T13
U1_T14: TP284.1, U1.T14
U1_T15: TP285.1, U1.T15
U1_T16: TP286.1, U1.T16
U1_T17: TP287.1, U1.T17
U1_T18: TP288.1, U1.T18
U1_U1: TP289.1, U1.U1
U1_U2: TP290.1, U1.U2
U1_U3: TP291.1, U1.U3
U1_U4: TP292.1, U1.U4
U1_U5: TP293.1, U1.U5
U1_U6: TP294.1, U1.U6
U1_U7: TP295.1, U1.U7
U1_U8: TP296.1, U1.U8
U1_U9: TP297.1, U1.U9
U1_U10: TP298.1, U1.U10
U1_U11: TP299.1, U1.U11
U1_U12: TP300.1, U1.U12
U1_U13: TP301.1, U1.U13
U1_U14: TP302.1, U1.U14
U1_U15: TP303.1, U1.U15
U1_U16: TP304.1, U1.U16
U1_U17: TP305.1, U1.U17
U1_U18: TP306.1, U1.U18
U1_V1: TP307.1, U1.V1
U1_V2: TP308.1, U1.V2
U1_V3: TP309.1, U1.V3
U1_V4: TP310.1, U1.V4
U1_V5: TP311.1, U1.V5
U1_V6: TP312.1, U1.V6
U1_V7: TP313.1, U1.V7
U1_V8: TP314.1, U1.V8
U1_V9: TP315.1, U1.V9
U1_V10: TP316.1, U1.V10
U1_V11: TP317.1, U1.V11
U1_V12: TP318.1, U1.V12
U1_V13: TP319.1, U1.V13
U1_V14: TP320.1, U1.V14
U1_V15: TP321.1, U1.V15
U1_V16: TP322.1, U1.V16
U1_V17: TP323.1, U1.V17
U1_V18: TP324.1, U1.V18

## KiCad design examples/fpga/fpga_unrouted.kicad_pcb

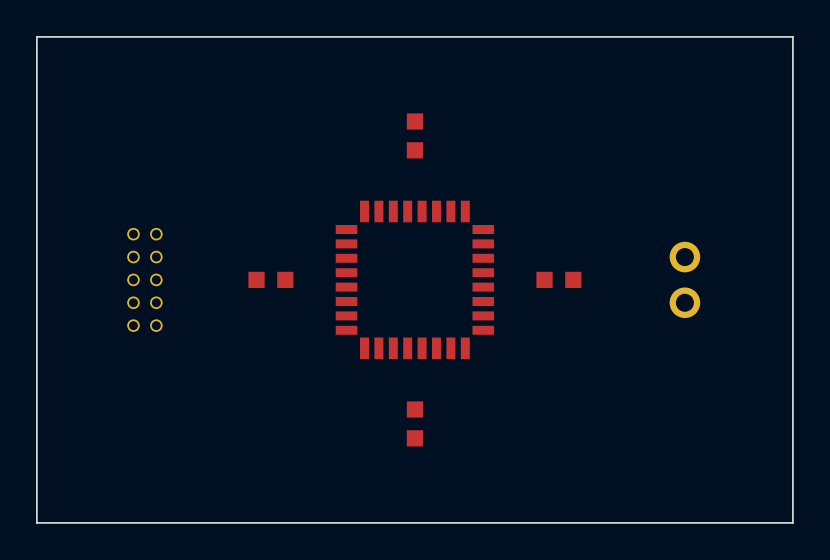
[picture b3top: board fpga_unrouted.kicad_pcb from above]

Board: 4 copper layers, 42.0 x 27.0 mm, 7 parts (0 on the bottom side), 9 nets, no tracks yet.

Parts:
C1, C2, C3, C4: 100nF; C_0603_1608Metric
J1: JTAG; PinHeader_2x05_P1.27mm_Vertical
J2: PWR; PinHeader_1x02_P2.54mm_Vertical
U1: FPGA; TQFP-32_7x7mm_P0.8mm

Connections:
GND: C1.2, C2.2, C3.2, C4.2, J2.2, U1.16, U1.32
GPIO1: U1.9, U1.25
GPIO2: U1.10, U1.26
SIG1: U1.5, U1.17
TCK: J1.4, U1.2
TDI: J1.8, U1.3
TDO: J1.6, U1.4
TMS: J1.2, U1.1
VCC: C1.1, C2.1, C3.1, C4.1, J2.1, U1.8, U1.24

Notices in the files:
parts and their libraries:
Copyright 2021 Accelerated Designs. All rights reserved.
